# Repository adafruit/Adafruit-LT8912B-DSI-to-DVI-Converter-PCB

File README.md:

## Adafruit LT8912B DSI to DVI Converter PCB

<a href="http://www.adafruit.com/products/6539"><br/>
Click here to purchase one from the Adafruit shop</a>

PCB files for the Adafruit LT8912B DSI to DVI Converter. 

Format is EagleCAD schematic and board layout
* https://www.adafruit.com/product/6539

### Description

You've likely used I2C or SPI to connect to small displays on your microcontroller: these two protocols are great for small OLEDs and TFTs, maxing out at about 320x480 pixels. If you want to go bigger maybe you've stretched into TTL displays like on our ESP32-S3 Qualia which can go to 720x720, but TTL displays use a LOT of pins, like 30+ and they max out due to the limits of sloshing data over a parallel interface. So, the MIPI alliance came up with a high speed serial interface for displays...big surprise they call it DSI (display serial interface). We're starting to see more and more chips that come with DSI - this interface has been available on the Raspberry Pi computer series for a long time but now the [ESP32-P4](https://www.adafruit.com/product/6536) has it too. And more chips are coming out with DSI support as it becomes widely adopted.

If you have a chip or computer with DSI you can connect many panel displays to it, and now thanks to the <b>Adafruit LT8912B DSI to DVI Converter</b> you can connect a DSI output to a DVI or HDMI monitor! This converter chip will take that DSI signal and squish it around to the right format and connector that many TVs and monitors use, you can even use an HDMI capture dongle if you want to pipe the signal into a computer. It works with up to 4 lanes for 1080p60 max resolution.

One side has a 22-pin 0.5mm pitch FPC connector, this is the "Raspberry Pi 5" standard pinout (also used on compute-module boards) and we also use in on our [ESP32-P4 boards](https://www.adafruit.com/product/6536). [To connect to something with a similar 22-pin FPC connector](https://www.adafruit.com/product/6035), use this flex cable. If you have an older Raspberry Pi or some other DSI emitter with the 15-pin 1mm pitch connector, [use an adapter converter cable like this one](https://www.adafruit.com/product/5821). <b>Note we don't include a cable with this adapter because we dont know which one you need, so pick that up separately!</b>

Once the FPC is connected, you do have to configure the LT8912B over I2C. Thankfully there's an I2C lane on the FPC cable [so you can use our Arduino or CircuitPython drivers](https://github.com/adafruit/Adafruit_LT8912B) to set up the LT8912B for the resolution that matches the DSI output (and, ideally one that the DVI monitor supports!) On Raspberry Pi, [there's a kernel module](https://github.com/raspberrypi/linux/pull/7725) you can use - a device tree overlay will configure the chip resolution. [Espressif has their own ESPIDF driver](https://components.espressif.com/components/espressif/esp_lcd_lt8912b) as well. Note that this chip requires signing an NDA to get full datasheet and driver support so we've cobbled together our support using publicly available info, and it works just fine - but we won't be able to provide a full datasheet. (You're free to contact/sign with the chip maker if you like for in-depth support)

Astute folks may remember that DVI/HDMI monitors also have an I2C device built-in on 0x50 for EDID detection so you can determine supported resolutions and modes. We connect those I2C lines (called DDC) to the same I2C lines on the FPC so you can configure the LT8912B and also read the EDID at the same connection. This is great 99% of the time. But! If you happen to be connecting to an RTD266x-driven monitor, which is common for small maker-friendly displays, that controller also uses a conflicting I2C address to the LT8912B. So, basically, if you are connecting to an RTD266x-controlled-monitor, switch the DDC connection switch to 'off' and then you can read the DDC over the Stemma QT port or breakout pads at the top, make sure its on a second I2C port.

Finally, the most observant of all may see the I2S pins broken out and ask: hey can I also pipe I2S in to have that audio played on the monitor in question? The answer is: maybe? We broke out those pins and tried hard to get I2S audio working, but given we don't have the proper NDA'd datasheet there's no working example. We're pretty sure it can be done but I2S input is unsupported. If you figure it out let us know!

We've tested this a bunch on the [ESP32-P4](https://www.adafruit.com/product/6536) and Raspberry Pi 5 - it ought to work on other DSI sources but we've not tried it out ourselves. Despite using the same connector as the HSTX this is not going to work with the RP2350. Check that your source uses the same pinout as the Raspberry Pi 5 to make sure it will work!

### License

Adafruit invests time and resources providing this open source design, please support Adafruit and open-source hardware by purchasing products from [Adafruit](https://www.adafruit.com)!

Designed by Limor Fried/Ladyada for Adafruit Industries.

Creative Commons Attribution/Share-Alike, all text above must be included in any redistribution. 
See license.txt for additional details.

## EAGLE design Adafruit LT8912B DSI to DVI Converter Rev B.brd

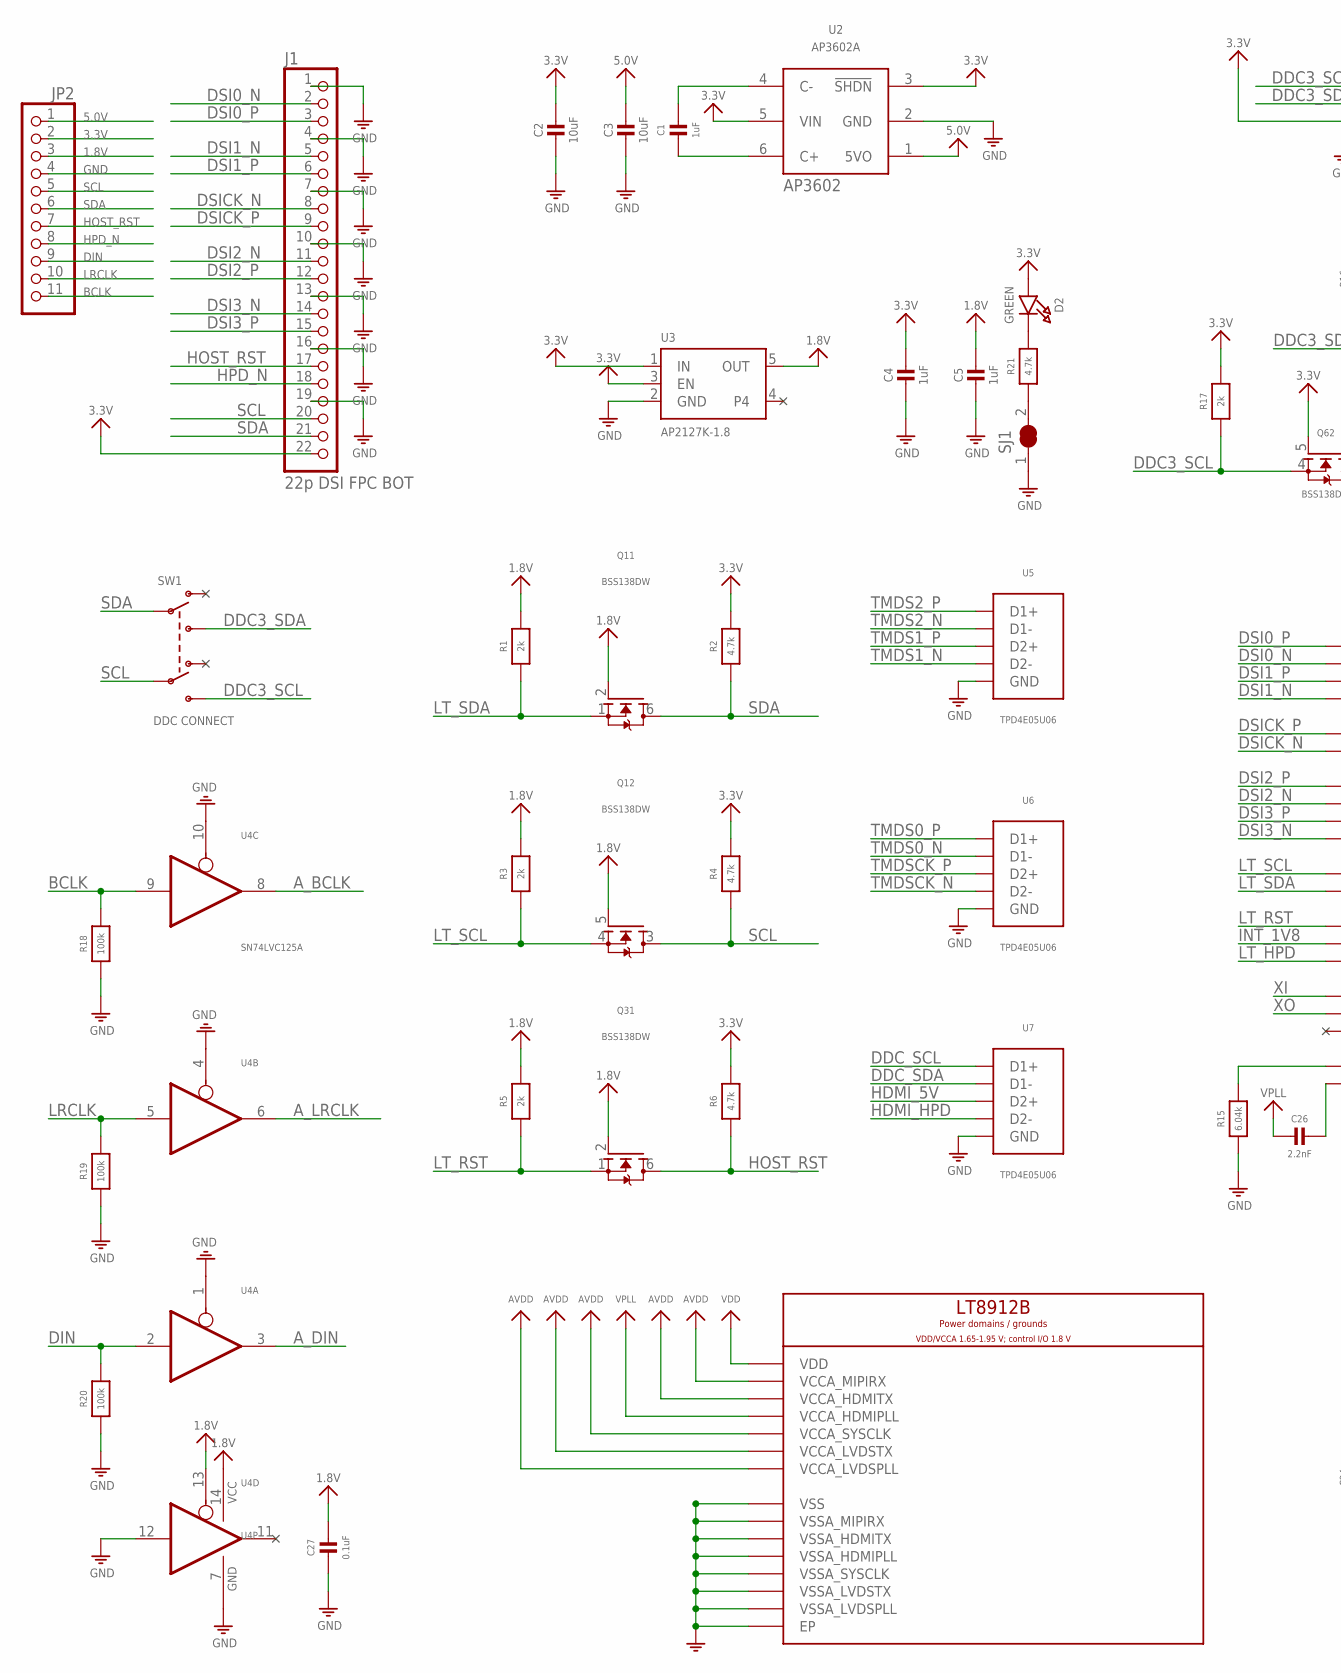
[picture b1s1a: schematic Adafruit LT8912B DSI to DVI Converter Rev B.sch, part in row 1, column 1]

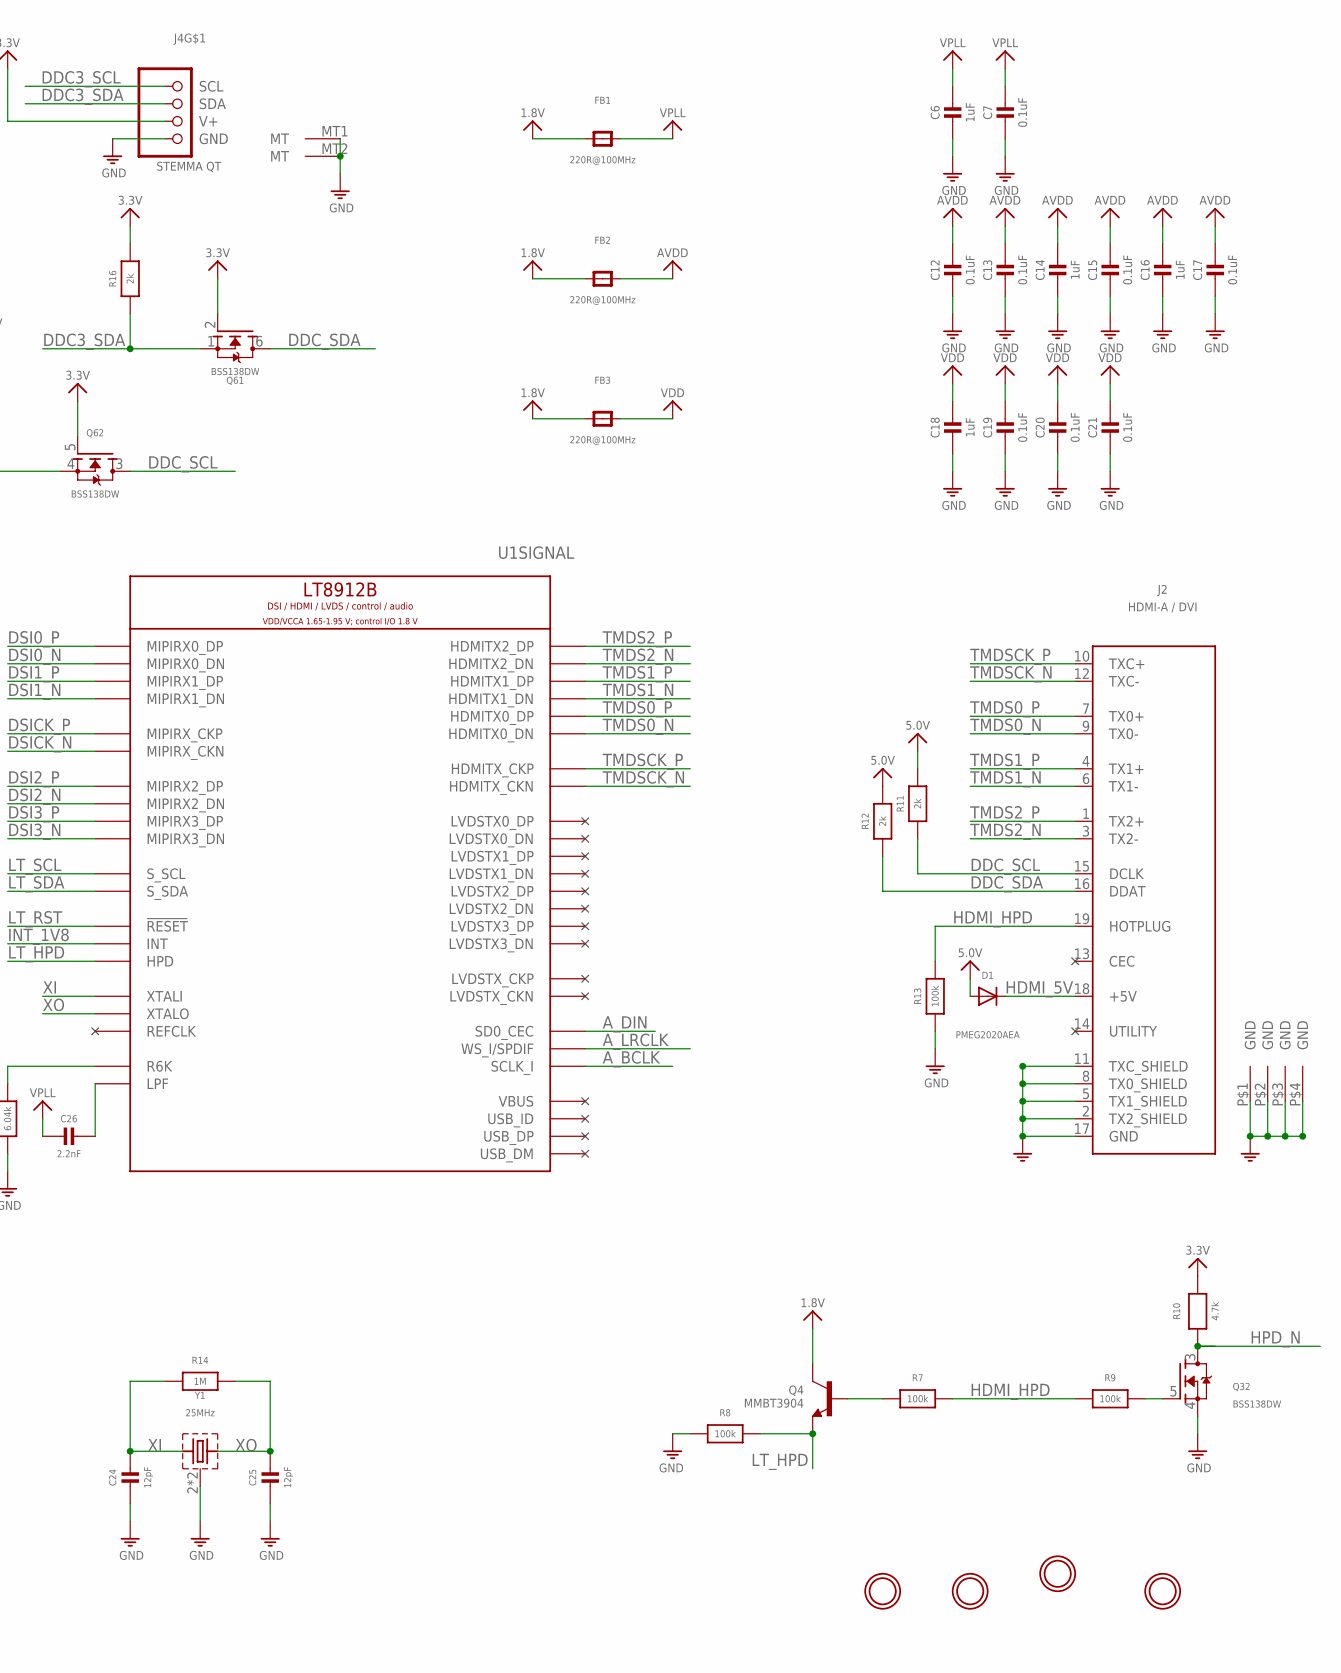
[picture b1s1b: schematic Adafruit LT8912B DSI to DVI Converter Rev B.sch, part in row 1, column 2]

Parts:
C1, C4, C5, C6, C14, C16, C18: 1uF; 0603-NO
C2, C3: 10uF; 0805-NO
C7, C12, C13, C15, C17, C19, C20, C21, C27: 0.1uF; 0603-NO
C24, C25: 12pF; 0603-NO
C26: 2.2nF; 0603-NO
D1: PMEG2020AEA; SOD-323F; MPN PMEG2020AEA; LCSC C389354
D2: GREEN; CHIPLED_0603_NOOUTLINE
FB1, FB2, FB3: 220R@100MHz; 0603-NO
J1: 22p DSI FPC BOT; FPC_22PIN; MPN AFC01-S22FCA-00; LCSC C262668
J2: HDMI-A / DVI; HDMI_MOLEX_47151-0001; MPN HDMI-001 19PCBTP; LCSC C138388
J4: STEMMA QT; JST_SH4
JP2: HEADER-1X11; 1X11_ROUND
Q1, Q3, Q6: BSS138DW; SOT363; MPN BSS138DW-7-F; JLC_ROTATION 270
Q4: MMBT3904; SOT23-R
R1, R3, R5, R11, R12, R16, R17: 2k; 0603-NO
R2, R4, R6, R10, R21: 4.7k; 0603-NO
R7, R8, R9, R13, R18, R19, R20: 100k; 0603-NO
R14: 1M; 0603-NO
R15: 6.04k; 0603-NO
SJ1: SOLDERJUMPER_CLOSED; SOLDERJUMPER_CLOSEDWIRE
SW1: DDC CONNECT; EG1390; MPN MS-22C01-G010; LCSC C2837066
U1: LT8912B; QFN64_7.5X7.5_P04_EP62_LT8912B; MPN LT8912B; LCSC C2892102
U2: AP3602A; SOT23-6; MPN AP3602AKTR-G1; LCSC C460358
U3: AP2127K-1.8; SOT23-5; MPN AP2127K-1.8TRG1; LCSC C151375
U4: SN74LVC125A; TSSOP14; MPN SN74LVC125APWR; LCSC C7813
U5, U6, U7: TPD4E05U06; USON10_1X2.5_P05_TPD4E05U06; MPN TPD4E05U06DQAR; LCSC C138714
U$1, U$2, U$3, U$4: MOUNTINGHOLE2.5; MOUNTINGHOLE_2.5_PLATED
Y1: 25MHz; CRYSTAL_2X1.6; MPN Q22FA12800569; LCSC C193187

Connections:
1.8V: C5.1, C27.1, FB1.1, FB2.1, FB3.1, JP2.3, Q1.2 (G), Q1.5 (G), Q3.2 (G), Q4.3 (C), R1.2, R3.2, R5.2, U3.5 (OUT), U4.13 (OE), U4.14 (VCC)
3.3V: C2.1, C4.1, D2.A, J1.22, J4.2 (V+), JP2.2, Q6.2 (G), Q6.5 (G), R2.2, R4.2, R6.2, R10.2, R16.2, R17.2, U2.3 (!SHDN), U2.5 (VIN), U3.1 (IN), U3.3 (EN)
5.0V: C3.1, D1.A, JP2.1, R11.2, R12.2, U2.1 (5VO)
AVDD: C12.1, C13.1, C14.1, C15.1, C16.1, C17.1, FB2.2, U1.5 (VCCA_MIPIRX), U1.26 (VCCA_HDMITX), U1.41 (VCCA_LVDSTX), U1.50 (VCCA_SYSCLK), U1.52 (VCCA_LVDSPLL)
A_BCLK: U1.60 (SCLK_I), U4.8 (O)
A_DIN: U1.58 (SD0_CEC), U4.3 (O)
A_LRCLK: U1.59 (WS_I/SPDIF), U4.6 (O)
BCLK: JP2.11, R18.2, U4.9 (I)
BIAS: R15.2, U1.13 (R6K)
DDC3_SCL: J4.4 (SCL), Q6.4 (S), R17.1, SW1.S2
DDC3_SDA: J4.3 (SDA), Q6.1 (S), R16.1, SW1.S1
DDC_SCL: J2.15 (DCLK), Q6.3 (D), R11.1, U7.1 (D1+), U7.10 (D1+)
DDC_SDA: J2.16 (DDAT), Q6.6 (D), R12.1, U7.2 (D1-), U7.9 (D1-)
DIN: JP2.9, R20.2, U4.2 (I)
DSI0_N: J1.2, U1.2 (MIPIRX0_DN)
DSI0_P: J1.3, U1.1 (MIPIRX0_DP)
DSI1_N: J1.5, U1.4 (MIPIRX1_DN)
DSI1_P: J1.6, U1.3 (MIPIRX1_DP)
DSI2_N: J1.11, U1.10 (MIPIRX2_DN)
DSI2_P: J1.12, U1.9 (MIPIRX2_DP)
DSI3_N: J1.14, U1.12 (MIPIRX3_DN)
DSI3_P: J1.15, U1.11 (MIPIRX3_DP)
DSICK_N: J1.8, U1.8 (MIPIRX_CKN)
DSICK_P: J1.9, U1.7 (MIPIRX_CKP)
FLY_+: C1.2, U2.6 (C+)
FLY_-: C1.1, U2.4 (C-)
GND: C2.2, C3.2, C4.2, C5.2, C6.2, C7.2, C12.2, C13.2, C14.2, C15.2, C16.2, C17.2, C18.2, C19.2, C20.2, C21.2, C24.2, C25.2, C27.2, J1.1, J1.4, J1.7, J1.10, J1.13, J1.16, J1.19, J2.2 (TX2_SHIELD), J2.5 (TX1_SHIELD), J2.8 (TX0_SHIELD), J2.11 (TXC_SHIELD), J2.17 (GND), J2.P$1 (GND), J2.P$2 (GND), J2.P$3 (GND), J2.P$4 (GND), J4.1 (GND), J4.MT1 (MT), J4.MT2 (MT), JP2.4, Q3.4 (S), R8.1, R13.1, R15.1, R18.1, R19.1, R20.1, SJ1.1, U1.6 (VSSA_MIPIRX), U1.17 (VSS), U1.23 (VSSA_HDMITX), U1.29 (VSSA_HDMITX), U1.32 (VSS), U1.36 (VSSA_HDMIPLL), U1.42 (VSSA_LVDSTX), U1.49 (VSSA_SYSCLK), U1.51 (VSSA_LVDSPLL), U1.56 (VSS), U1.EP, U2.2 (GND), U3.2 (GND), U4.1 (OE), U4.4 (OE), U4.7 (GND), U4.10 (OE), U4.12 (I), U5.3 (GND), U5.8 (GND), U6.3 (GND), U6.8 (GND), U7.3 (GND), U7.8 (GND), Y1.2 (GND), Y1.4 (GND)
HDMI_5V: D1.C, J2.18 (+5V), U7.4 (D2+), U7.7 (D2+)
HDMI_HPD: J2.19 (HOTPLUG), R7.1, R9.1, R13.2, U7.5 (D2-), U7.6 (D2-)
HOST_RST: J1.17, JP2.7, Q3.6 (D), R6.1
HPD_BASE: Q4.1 (B), R7.2
HPD_HOST_B: Q3.5 (G), R9.2
HPD_N: J1.18, JP2.8, Q3.3 (D), R10.1
INT_1V8: U1.63 (INT)
LPF: C26.1, U1.35 (LPF)
LRCLK: JP2.10, R19.2, U4.5 (I)
LT_HPD: Q4.2 (E), R8.2, U1.14 (HPD)
LT_RST: Q3.1 (S), R5.1, U1.64 (!RESET)
LT_SCL: Q1.4 (S), R3.1, U1.62 (S_SCL)
LT_SDA: Q1.1 (S), R1.1, U1.61 (S_SDA)
unnamed: R21.1, SJ1.2
unnamed: D2.C, R21.2
SCL: J1.20, JP2.5, Q1.3 (D), R4.1, SW1.P2
SDA: J1.21, JP2.6, Q1.6 (D), R2.1, SW1.P1
TMDS0_N: J2.9 (TX0-), U1.24 (HDMITX0_DN), U6.2 (D1-), U6.9 (D1-)
TMDS0_P: J2.7 (TX0+), U1.25 (HDMITX0_DP), U6.1 (D1+), U6.10 (D1+)
TMDS1_N: J2.6 (TX1-), U1.27 (HDMITX1_DN), U5.5 (D2-), U5.6 (D2-)
TMDS1_P: J2.4 (TX1+), U1.28 (HDMITX1_DP), U5.4 (D2+), U5.7 (D2+)
TMDS2_N: J2.3 (TX2-), U1.30 (HDMITX2_DN), U5.2 (D1-), U5.9 (D1-)
TMDS2_P: J2.1 (TX2+), U1.31 (HDMITX2_DP), U5.1 (D1+), U5.10 (D1+)
TMDSCK_N: J2.12 (TXC-), U1.21 (HDMITX_CKN), U6.5 (D2-), U6.6 (D2-)
TMDSCK_P: J2.10 (TXC+), U1.22 (HDMITX_CKP), U6.4 (D2+), U6.7 (D2+)
VDD: C18.1, C19.1, C20.1, C21.1, FB3.2, U1.18 (VDD), U1.33 (VDD), U1.57 (VDD)
VPLL: C6.1, C7.1, C26.2, FB1.2, U1.34 (VCCA_HDMIPLL)
XI: C24.1, R14.1, U1.53 (XTALI), Y1.1
XO: C25.1, R14.2, U1.54 (XTALO), Y1.3 (2)

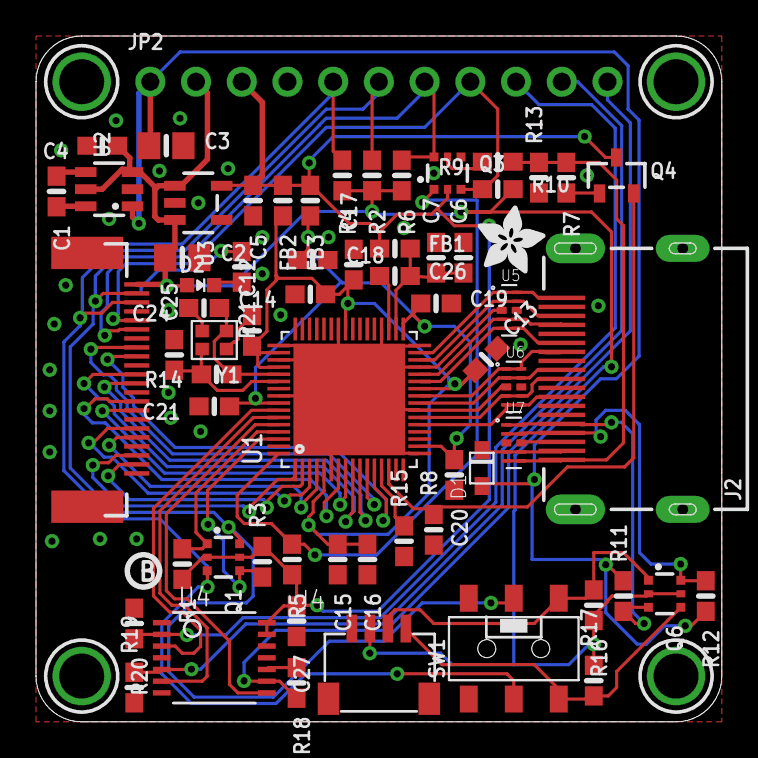
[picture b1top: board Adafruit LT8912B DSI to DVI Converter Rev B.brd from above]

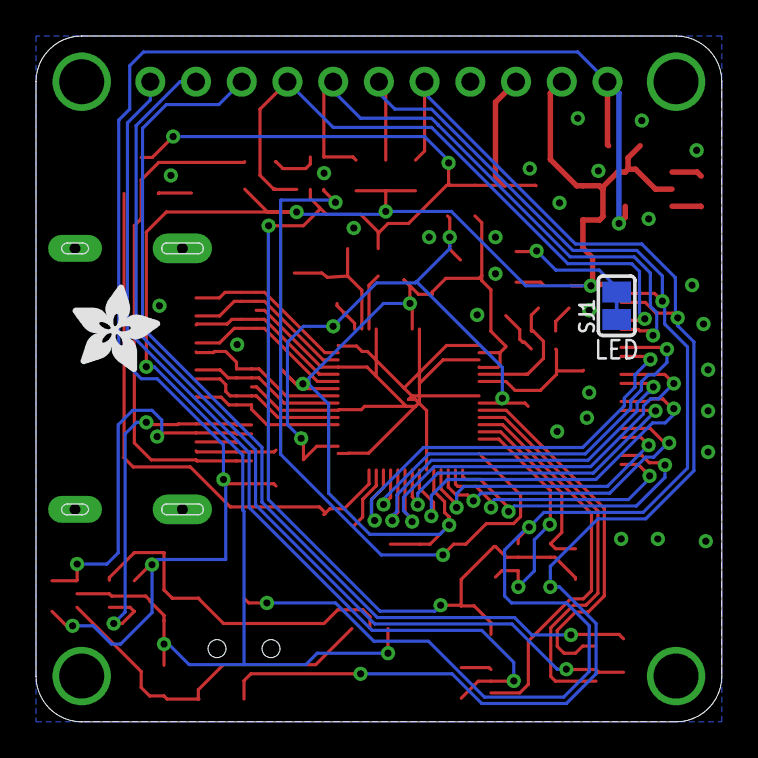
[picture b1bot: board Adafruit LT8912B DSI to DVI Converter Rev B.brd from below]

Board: 2 copper layers, 38.1 x 38.1 mm, 108 parts (18 on the bottom side), 55 nets.

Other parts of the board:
PLABEL0: PLABEL0
PLABEL1: PLABEL1
PLABEL2: PLABEL2
PLABEL3: PLABEL3
PLABEL4: PLABEL4
PLABEL5: PLABEL5
PLABEL6: PLABEL6
PLABEL7: PLABEL7
PLABEL8: PLABEL8
PLABEL9: PLABEL9
PLABEL10: PLABEL10
PLABEL11: PLABEL11
PLABEL12: PLABEL12
PLABEL13: PLABEL13
PLABEL14: PLABEL14
PLABEL15: PLABEL15
PLABEL16: PLABEL16
PLABEL17: PLABEL17
PLABEL18: PLABEL18
PLABEL19: PLABEL19
PLABEL20: PLABEL20
PLABEL21: PLABEL21
PLABEL22: PLABEL22
PLABEL23: PLABEL23
PLABEL24: PLABEL24
PLABEL25: PLABEL25
PLABEL26: PLABEL26
PLABEL27: PLABEL27
PLABEL28: PLABEL28
PLABEL29: PLABEL29
PLABEL30: PLABEL30
PLABEL31: PLABEL31
PLABEL32: PLABEL32
PLABEL33: PLABEL33
PLABEL34: PLABEL34
PLABEL35: PLABEL35
U$5: ADAFRUIT_3.5MM
U$6: PCBFEAT-REV-040
U$7: ADAFRUIT_5MM

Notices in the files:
parts and their libraries:
microbuilder: This work is placed in the public domain, and may be freely used for commercial and non-commercial work with the following conditions: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
